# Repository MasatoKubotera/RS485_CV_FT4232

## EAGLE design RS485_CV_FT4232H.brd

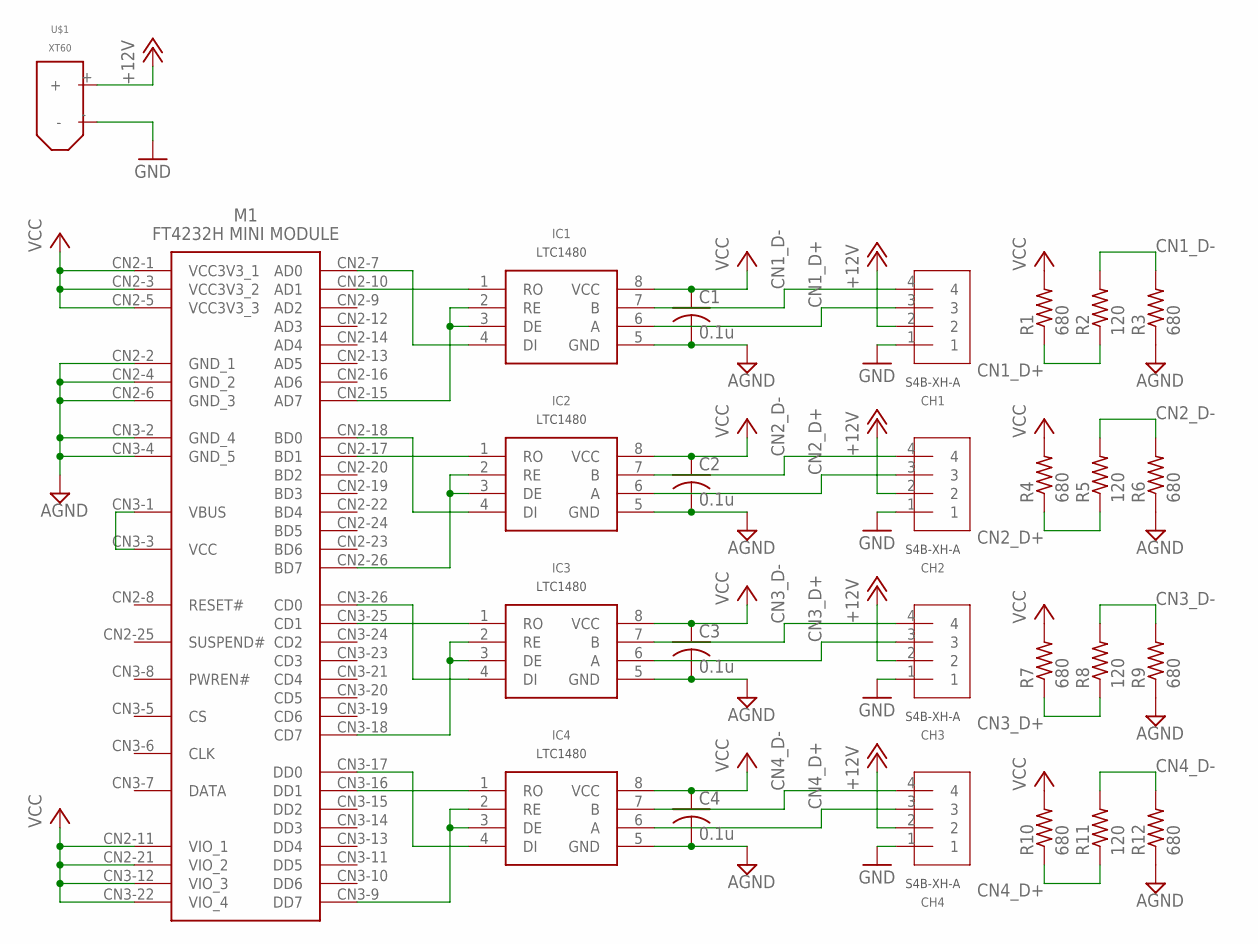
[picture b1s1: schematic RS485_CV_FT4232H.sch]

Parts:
C1, C2, C3, C4: 0.1u; C0603
CH1, CH2, CH3, CH4: S4B-XH-A
IC1, IC2, IC3, IC4: LTC1480
M1: FT4232H_MINI_MODULE
R1, R3, R4, R6, R7, R9, R10, R12: 680; R0603
R2, R5, R8, R11: 120; R0603
U$1: XT60PT-M

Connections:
+12V: CH1.2, CH2.2, CH3.2, CH4.2, U$1.+
AGND: C1.2, C2.2, C3.2, C4.2, IC1.5 (GND), IC2.5 (GND), IC3.5 (GND), IC4.5 (GND), M1.CN2-2 (GND_1), M1.CN2-4 (GND_2), M1.CN2-6 (GND_3), M1.CN3-2 (GND_4), M1.CN3-4 (GND_5), R3.1, R6.1, R9.1, R12.1
CN1_D+: CH1.3, IC1.6 (A), R1.1, R2.1
CN1_D-: CH1.4, IC1.7 (B), R2.2, R3.2
CN2_D+: CH2.3, IC2.6 (A), R4.1, R5.1
CN2_D-: CH2.4, IC2.7 (B), R5.2, R6.2
CN3_D+: CH3.3, IC3.6 (A), R7.1, R8.1
CN3_D-: CH3.4, IC3.7 (B), R8.2, R9.2
CN4_D+: CH4.3, IC4.6 (A), R10.1, R11.1
CN4_D-: CH4.4, IC4.7 (B), R11.2, R12.2
GND: CH1.1, CH2.1, CH3.1, CH4.1, U$1.-
unnamed: IC1.4 (DI), M1.CN2-7 (AD0)
unnamed: IC1.2 (RE), IC1.3 (DE), M1.CN2-15 (AD7)
unnamed: IC2.4 (DI), M1.CN2-18 (BD0)
unnamed: IC2.1 (RO), M1.CN2-17 (BD1)
unnamed: IC3.4 (DI), M1.CN3-26 (CD0)
unnamed: IC3.1 (RO), M1.CN3-25 (CD1)
unnamed: IC4.4 (DI), M1.CN3-17 (DD0)
unnamed: IC4.1 (RO), M1.CN3-16 (DD1)
unnamed: IC1.1 (RO), M1.CN2-10 (AD1)
unnamed: IC2.2 (RE), IC2.3 (DE), M1.CN2-26 (BD7)
unnamed: IC3.2 (RE), IC3.3 (DE), M1.CN3-18 (CD7)
unnamed: IC4.2 (RE), IC4.3 (DE), M1.CN3-9 (DD7)
unnamed: M1.CN3-1 (VBUS), M1.CN3-3 (VCC)
VCC: C1.1, C2.1, C3.1, C4.1, IC1.8 (VCC), IC2.8 (VCC), IC3.8 (VCC), IC4.8 (VCC), M1.CN2-1 (VCC3V3_1), M1.CN2-3 (VCC3V3_2), M1.CN2-5 (VCC3V3_3), M1.CN2-11 (VIO_1), M1.CN2-21 (VIO_2), M1.CN3-12 (VIO_3), M1.CN3-22 (VIO_4), R1.2, R4.2, R7.2, R10.2

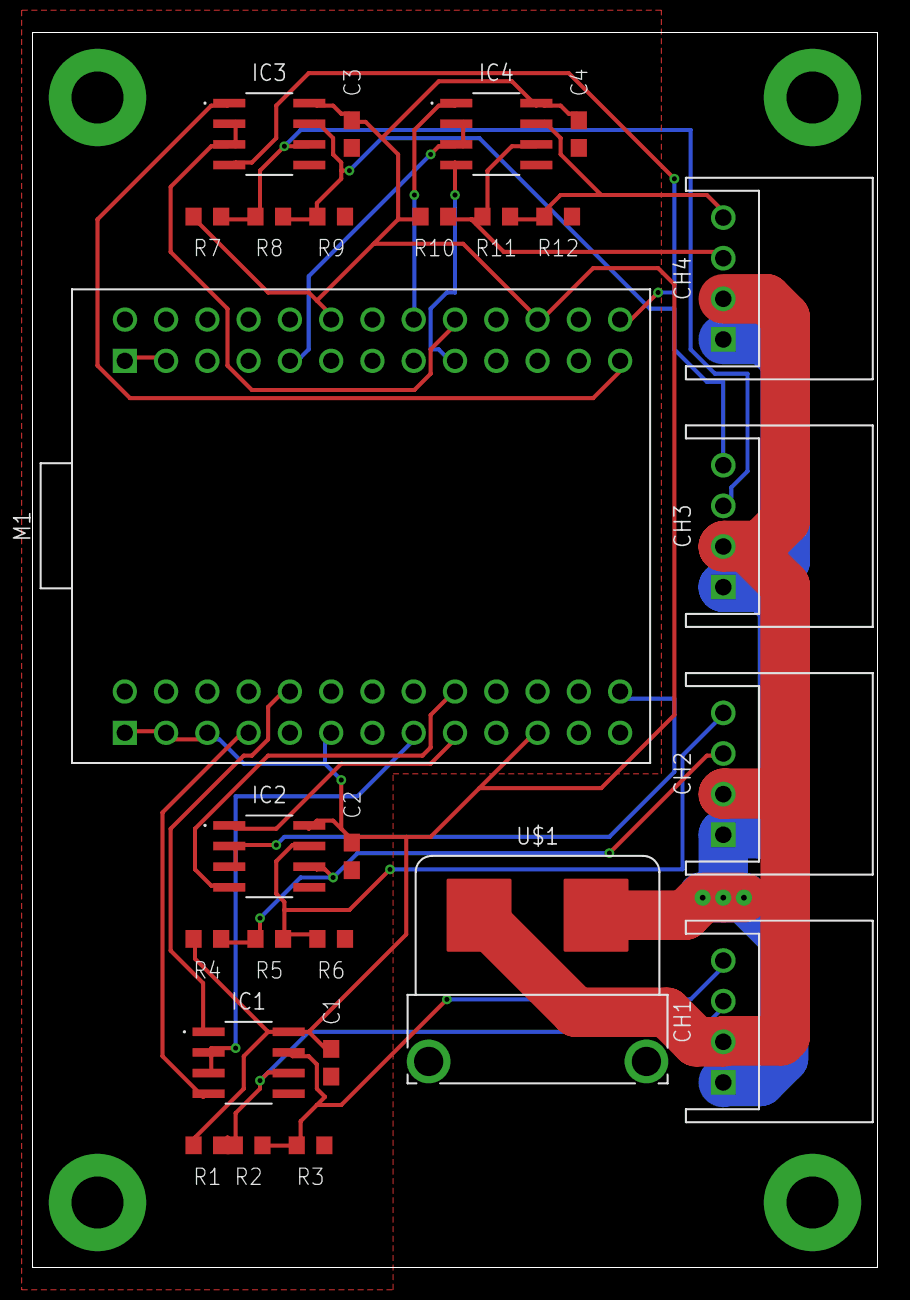
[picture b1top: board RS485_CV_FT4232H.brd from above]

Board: 2 copper layers, 52.0 x 76.0 mm, 26 parts (0 on the bottom side), 25 nets.

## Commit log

2022-01-31 make Quad RS485 control circuit using FT4232
